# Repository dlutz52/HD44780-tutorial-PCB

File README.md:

# HD44780 Tutorial PCB

My inspiration for this PCB came from following Ian Ward's project on his web site:

[LCD2004 20×4 LCD Character Display with HD44780 Tutorial](https://excess.org/lcd2004-tutorial/)

# HD44780 Tutorial PCB BOM

## Wed, Mar 20, 2024, 05:20:29

## Component Count: 19

Ref | Qty | Value | Vendor\Part # | Description
----|-----|-------|---------------|-----------
C1, C2 | 2 | .01uF | Digikey\FG28C0G1H103JNT06 | Unpolarized capacitor 
D1 | 1 | RED | Generic | LED\3mm\Red 
D2 | 1 | BLUE | Generic | LED\3mm\Blue 
D3 | 1 | 8_SEG_LED  BAR_GRAPH (RED) | Generic | LED Bar Graph\Red\1x8 
D4 | 1 | GREEN | Generic | LED\3mm\Green 
D5 | 1 | YELLOW | Generic | LED\3mm\Yellow
J1 | 1 | PinSocket_1x16_P2.54mm_Vertical | Generic | Female Pin Header\1x16\2.54mm pitch
J2 | 1 | UJC-HP-M-G-5-MSMT-TR | Digikey\2223-UJC-HP-M-G-5-MSMT-TRDKR-ND | Type C/20 VDC/3A/Horizontal/6 Pin/Power Only
R1, R5, R6, R9 | 4 | 330ohm | Digikey\13-MFR-25FRF52-330RCT-ND | Resistor\330 Ohm\1%\1/4W\Axial
R2, R3, R4 | 3 | 1Kohm | Digikey\13-MFR-25FTE52-1KCT-ND | Resistor\1Kohm\1%\1/4W\Axial
R7, R8 | 2 | 5.1Kohm | Digikey\13-MFR-25FTE52-5K1CT-ND | Resistor\5K1ohm\1%\1/4W\Axial
RN1 | 1 | 470ohm | Digikey\4609X-101-471LF-ND | Resistor Array\ 8 Resistors\470ohm\9SIP
RN2 | 1 | 1Kohm | Digikey\4609X-101-102LF-ND | Resistor Array\ 8 Resistors\1Kohm\9SIP
RV1, RV2 | 2 | 5Kohm | Digikey\3386P-1-502LF | Trimmer Pot\5Kohms\0.5W\1/2W\Through Hole
S1 | 1 | TL2230 | Digikey\EG6031-ND | Switch\Pushbutton\DPDT\Through Hole
SW1 | 1 | REG SELECT | Digikey\450-1654-ND | Switch\Tactile\SPST-NO\0.05A\24V\Through Hole
SW2 | 1 | ENABLE | Digikey\450-1654-ND | Switch\Tactile\SPST-NO\0.05A\24V\Through Hole
SW3 | 1 | DS02C-254-1L-08BE | Digikey\2223-DS02C-254-1L-08BE-ND | Switch\Piano\8-DIP\SPST\25mA\24V\Through Hole

The LCD and its 16-pin male header are represented only with 3D models, but you need a 2004 LCD with a soldered 16-pin male header with a pitch of 2.54mm to plug into the 16 pin female header to complete this PCB. I have found the best place to get these is on eBay.

Do NOT try to use a 2004 LCD with an I<sup>2</sup>C adapter on it.

Most symbols/footprints/models are contained under the 'libraries' directory. Capacitors, resistors and LEDs use KiCad symbols/footprints/models.

KiCad 7.0.10 was used to create this PCB. KiCad 8.0.1 is out now and this project opens in that version. The newer KiCad will warn that this project was created in previous version and will be saved in a the newer format. When closing the schematic or a PCB just discard any changes. If you do not you will not be able to use KiCad 7 any more without difficulties.

Some models in KiCad's 3D view will display an appropriate socket under them but these can be omitted on the PCB - they are used to make it easier to replace any components should they need it in the future.

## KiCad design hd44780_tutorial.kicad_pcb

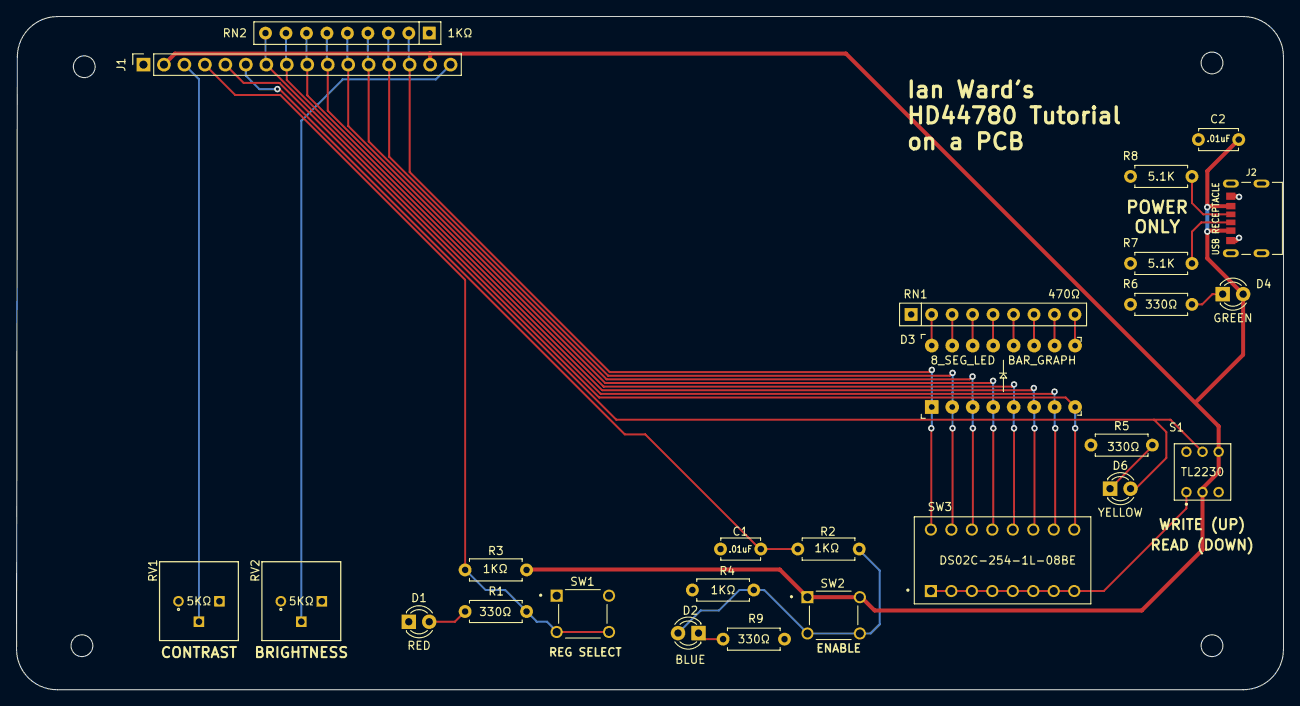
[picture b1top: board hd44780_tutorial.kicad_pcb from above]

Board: 2 copper layers, 157.2 x 83.5 mm, 30 parts (0 on the bottom side), 31 nets.

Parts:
C1, C2: .01uF; C_Disc_D4.7mm_W2.5mm_P5.00mm
D1: RED; LED_D3.0mm
D2: BLUE; LED_D3.0mm
D3: 8_SEG_LED BAR_GRAPH; LED_Bar_Graph_8_SEG_SOCKET
D4: GREEN; LED_D3.0mm
D6: YELLOW; LED_D3.0mm
H1, H2, H3, H4: MountingHole; MountingHole_2.7mm_M2.5
J1: LCD_2004_PinSocket_1x16_P2.54mm_Vertical
J2: USB RECEPTACLE; CUI_UJC-HP-M-G-5-MSMT-TR
R1, R5, R6, R9: 330Ω; R_Axial_DIN0207_L6.3mm_D2.5mm_P7.62mm_Horizontal
R2, R3, R4: 1KΩ; R_Axial_DIN0207_L6.3mm_D2.5mm_P7.62mm_Horizontal
R7, R8: 5.1K; R_Axial_DIN0207_L6.3mm_D2.5mm_P7.62mm_Horizontal
RN1: 470Ω; R_Array_SIP9
RN2: 1KΩ; R_Array_SIP9
RV1, RV2: 5KΩ; BOURNE-3386P
S1: TL2230; TL2230EEF140
SW1: REG SELECT; SW_1825967-1
SW2: ENABLE; SW_1825967-1
SW3: DS02C-254-1L-08BE; SW_DS02C-254-1L-08BE

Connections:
+5V: C2.1, D4.2 (A), J1.2, J1.15, J2.A9 (V-BUS), J2.B9 (V-BUS__1), R3.2, S1.2 (COM_1), S1.6 (NO_2), SW2.1, SW2.2
/BLK: J1.16, RV2.2
/D0: D3.8, J1.7, RN2.9 (R8), SW3.8B
/D1: D3.7, J1.8, RN2.8 (R7), SW3.7B
/D2: D3.6, J1.9, RN2.7 (R6), SW3.6B
/D3: D3.5, J1.10, RN2.6 (R5), SW3.5B
/D4: D3.4, J1.11, RN2.5 (R4), SW3.4B
/D5: D3.3, J1.12, RN2.4 (R3), SW3.3B
/D6: D3.2, J1.13, RN2.3 (R2), SW3.2B
/D7: D3.1, J1.14, RN2.2 (R1), SW3.1B
/E: C1.1, J1.6, R2.2
/RS: J1.4, R1.1, R3.1, SW1.3, SW1.4
/RW: D6.2 (A), J1.5, S1.5 (COM_2)
/V0: J1.3, RV1.2
GND: C1.2, C2.2, D1.1 (K), J1.1, J2.A12 (GND), J2.B12 (GND__1), R4.1, R5.1, R6.1, R7.2, R8.2, R9.2, RN1.1 (common), RN2.1 (common), RV1.3, RV2.3, S1.4 (NC_2), SW1.1, SW1.2
unnamed: D1.2 (A), R1.2
unnamed: D2.2 (A), R2.1, R4.2, SW2.3, SW2.4
unnamed: D2.1 (K), R9.1
unnamed: D4.1 (K), R6.2
unnamed: D6.1 (K), R5.2
unnamed: J2.A5 (CC1), R7.1
unnamed: J2.B5 (CC2), R8.1
unnamed: D3.16, RN1.2 (R1)
unnamed: D3.15, RN1.3 (R2)
unnamed: D3.14, RN1.4 (R3)
unnamed: D3.13, RN1.5 (R4)
unnamed: D3.12, RN1.6 (R5)
unnamed: D3.11, RN1.7 (R6)
unnamed: D3.10, RN1.8 (R7)
unnamed: D3.9, RN1.9 (R8)
unnamed: S1.1 (NC_1), SW3.1A, SW3.2A, SW3.3A, SW3.4A, SW3.5A, SW3.6A, SW3.7A, SW3.8A

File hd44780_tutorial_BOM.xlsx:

# | Reference | Qty | Value | Footprint | Vendor\Part # | Vendor URL | Datasheet | Description
1 | C1, C2 | 2 | .01uF | Capacitor_THT:C_Disc_D4.7mm_W2.5mm_P5.00mm | Digikey\445-173474-1-ND | https://www.digikey.com/en/products/detail/tdk-corporation/F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 | https://product.tdk.com/en/system/files?file=dam/doc/product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 | Unpolarized capacitor
2 | D1 | 1 | RED | LED_THT:LED_D3.0mm | Generic |  |  | LED\3mm\Red
3 | D2 | 1 | BLUE | LED_THT:LED_D3.0mm | Generic |  |  | LED\3mm\Blue
4 | D3 | 1 | 8_SEG_LED BAR_GRAPH (RED) | footprints:LED_Bar_Graph_8_SEG_SOCKET | Generic |  |  | LED Bar Graph\Red\1x8
5 | D4 | 1 | GREEN | LED_THT:LED_D3.0mm | Generic |  |  | LED\3mm\Green
6 | D6 | 1 | YELLOW | LED_THT:LED_D3.0mm | Generic |  |  | LED\3mm\Yellow
7 | H1, H2, H3, H4 | 4 | MountingHole | MountingHole:MountingHole_2.7mm_M2.5 | KiCad |  |  | M2.5
8 | J1 | 1 | LCD_2004_PinSocket_1x16_P2.54mm_Vertical | footprints:LCD_2004_PinSocket_1x16_P2.54mm_Vertical | Generic |  |  | Female Pin Header\1x16\2.54mm pitch
9 | J2 | 1 | UJC-HP-M-G-5-MSMT-TR | footprints:CUI_UJC-HP-3-SMT-TR | Digikey\2223-UJC-HP-M-G-5-MSMT-TRDKR-ND | https://www.digikey.com/en/products/detail/cui-devices/UJC-H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 | https://www.cuidevices.com/product/resource/ujc-hp-m-g-5-msm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 | Type C, 20 VDC, 3A, Horizontal, Power Only
10 | R1, R5, R6, R9 | 4 | 330ohm | Resistor_THT:R_Axial_DIN0207_L6.3mm_D2.5mm_P7.62mm_Horizontal | Digikey\13-MFR-25FRF52-330RCT-ND | https://www.digikey.com/en/products/detail/yageo/MFR-25FRF52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 | https://www.yageo.com/upload/media/product/app/datasheet/lr/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 | Resistor\330ohm\1%\1/4W\Axial
11 | R2, R3, R4 | 3 | 1Kohm | Resistor_THT:R_Axial_DIN0207_L6.3mm_D2.5mm_P7.62mm_Horizontal | Digikey\13-MFR-25FTE52-1KCT-ND | https://www.digikey.com/en/products/detail/yageo/MFR-25FTE52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 | https://www.yageo.com/upload/media/product/app/datasheet/lr/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 | Resistor\1Kohm\1%\1/4W\Axial
12 | R7, R8 | 2 | 5.1Kohm | Resistor_THT:R_Axial_DIN0207_L6.3mm_D2.5mm_P7.62mm_Horizontal | Digikey\13-MFR-25FTE52-5K1CT-ND | https://www.digikey.com/en/products/detail/yageo/MFR-25FTE52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 | https://www.yageo.com/upload/media/product/app/datasheet/lr/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 | Resistor\5K1ohm\1%\1/4W\Axial
13 | RN1 | 1 | 470ohm | footprints:R_Array_SIP9 | Digikey\4609X-101-471LF-ND | https://www.digikey.com/en/products/detail/bourns-inc/4609X-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 | https://www.bourns.com/docs/Product-Datasheets/4600x.pdf | Resistor Array\ 8 Resistors\470ohm\9SIP
14 | RN2 | 1 | 1Kohm | footprints:R_Array_SIP9 | Digikey\4609X-101-102LF-ND | https://www.digikey.com/en/products/detail/bourns-inc/4609X-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 | https://www.bourns.com/docs/Product-Datasheets/4600x.pdf | Resistor Array\ 8 Resistors\1Kohm\9SIP
15 | RV1, RV2 | 2 | 5Kohm | footprints:BOURNE-3386P | Digikey\3386P-1-502LF | https://www.digikey.com/en/products/detail/bourns-inc/3386P-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 | https://www.bourns.com/docs/Product-Datasheets/3386.pdf | Trimmer Pot\5kohms\0.5W\1/2W\Through Hole
16 | S1 | 1 | TL2230 | footprints:TL2230EEF140 | Digikey\EG6031-ND | https://www.digikey.com/en/products/detail/e-switch/TL2230EE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 | https://eswitch.wpengine.com/wp-content/uploads/2022/06/TL22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 | Switch\Pushbutton\DPDT\Through Hole
17 | SW1 | 1 | REG SELECT | footprints:SW_1825967-1 | Digikey\450-1654-ND | https://www.digikey.com/en/products/detail/te-connectivity-a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 | https://www.te.com/usa-en/product-1825967-1.datasheet.pdf | Switch\Tactile\SPST-NO\0.05A\24V\Through Hole
18 | SW2 | 1 | ENABLE | footprints:SW_1825967-1 | Digikey\450-1654-ND | https://www.digikey.com/en/products/detail/te-connectivity-a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 | https://www.te.com/usa-en/product-1825967-1.datasheet.pdf | Switch\Tactile\SPST-NO\0.05A\24V\Through Hole
19 | SW3 | 1 | DS02C-254-1L-08BE | footprints:SW_DS02C-254-1L-08BE | Digikey\2223-DS02C-254-1L-08BE-ND | https://www.digikey.com/en/products/detail/cui-devices/DS02C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 | https://www.cuidevices.com/product/resource/ds02-254.pdf | Switch\Piano\8-DIP\SPST\0.025mA\24V\Through Hole

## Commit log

2024-03-05 Modified .gitignore
2024-03-05 Removing gerber ZIP file from repo
2024-03-05 Renamed BOM file
2024-03-05 Add jpg of baord front
2024-03-05 Added README.md
2024-03-05 Fixed some labels on PCB and made new JPG
2024-03-05 Added notice of Ian Ward's video in README.md
2024-03-05 Futzing with README.md
2024-03-06 Fixed wiring on the TL2230 switch. Made more space between switches and LEDs. New gerbers and JPEG.
2024-03-07 Final changes to create Version 1.0. Added logo footprints and moved description to back of board. Added title to front of board. Rebuilt gerber/drill files.
2024-03-14 Adjusted some copper tracks. Added Lutzcraft logo to local footprint library.
2024-03-15 Tried a new USB-C port and hate it. Prfeparing to revert to get rid of it.
2024-03-15 Revert "Tried a new USB-C port and hate it. Prfeparing to revert to get rid of it."
    This reverts commit 31f363ccd091cdbcf9bc00afb548c8c72483716e.
2024-03-15 Adjusted some copper tracks. Made all resistors horizontal. Added 1K network resistor for LCD data lines. Updated version number to 1.0a and date to 3/15/2024.
2024-03-17 Determined that adding 1K resistor to SW2 fixes the problem with this board. Created new gerber/drill files.
2024-03-17 Brought value of USB connector to front silkscreen.
2024-03-18 Delete hd44780_tutorial - Copy.kicad_pcb
    Never should have been committed
2024-03-18 Delete hd44780_tutorial - Copy.kicad_sch
    Never should have been committed
2024-03-18 Added *copy.kicad_sch and *copy.kicad_pcb to .gitignore after having deleted two such files online. Minor edits in hd44780_tutorial.kicad_sch
2024-03-18 Updated front/back boards images.
2024-03-19 Changed URLs to point to Ian's web site after his suggestion. Moved the RS track so it did not need a via. Regenerated gerber/drill files. Updated front and back images.
2024-03-19 Moved USB connector closer to edge of board.
2024-03-19 Updated gerber/drill files. Updated front image.
2024-03-21 Test of table in README.md
2024-03-21 Moved footprint/model for USB-C connector to local library. Updated BOM. Updated images. Regenerated gerber/drill files.
2024-03-21 Another README.md test.
2024-03-21 Updated XLSX BOM and README.md
2024-03-21 Another README.md change.
2024-03-21 Change name and value of USB footprint to be correct.
2024-03-21 Updated USB model to match symbol and fooprint.
2024-03-21 Removed mounting holes from BOM.
2024-03-21 Final changes to README.md
2024-03-21 Adding Google Search verification file.
2024-03-21 Create LICENSE
2024-03-21 Create LICENSE
    Added GNU General Public License - v3
2024-03-22 Deleted unused Gerbers/hd44780_tutorial-User_Drawings.gbr
2024-03-27 Updated README.md about no I2C adapter on LCD 2004.
2024-03-29 Minor edits to README.md. Added PDF of schematic for non-KiCad users.
2024-10-01 Changed project footprint/symbols directory paths from footprints/hd44780_tutorial to HD44780-tutorial-PCB/HD44780-tutorial-PCB.
2024-10-01 Last Kicad v7 version.
2024-10-01 First Kicad v8 version.
2025-05-11 Minor edits
